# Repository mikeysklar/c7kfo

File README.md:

# c7kfo
c7k flat out

Two handed super flat chording keyboard.

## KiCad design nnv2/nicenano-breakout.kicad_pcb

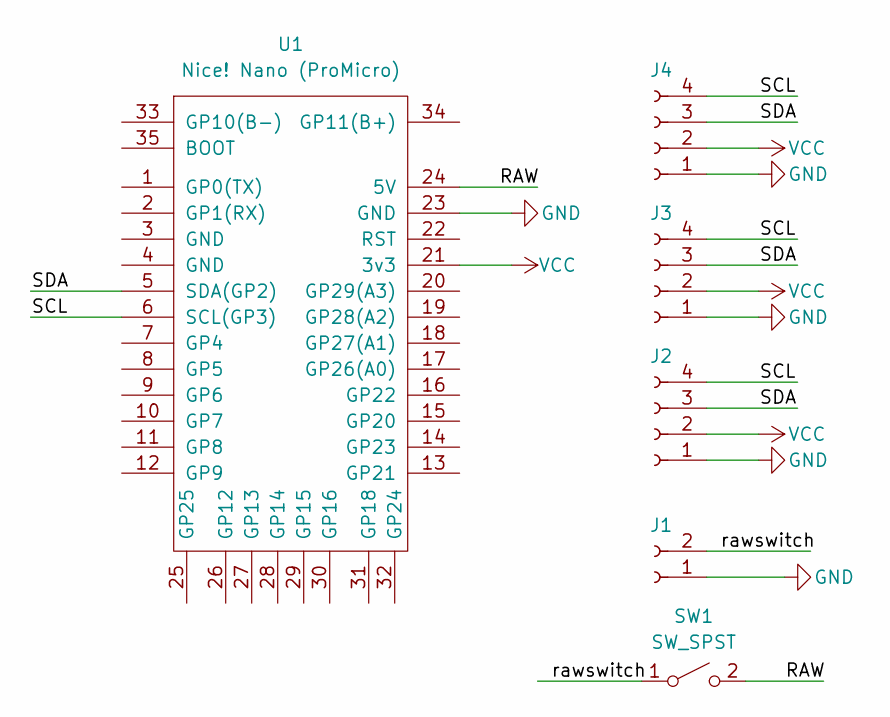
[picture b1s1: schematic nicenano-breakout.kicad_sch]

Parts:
J1: Conn_01x02_Socket; JST_PH_S2B-PH-SM4-TB_1x02-1MP_P2.00mm_Horizontal
J2, J3, J4: Conn_01x04_Socket; JST_SH4
SW1: SW_SPST; SW_SPDT_CK_JS102011SAQN
U1: Nice! Nano (ProMicro); SuperMini NRF52840

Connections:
/RAW: SW1.2 (B), U1.24 (5V)
/SCL: J2.4, J3.4, J4.4, U1.6 (SCL(GP3))
/SDA: J2.3, J3.3, J4.3, U1.5 (SDA(GP2))
/rawswitch: J1.2, SW1.1 (A)
GND: J1.1, J2.1, J3.1, J4.1, U1.23 (GND)
VCC: J2.2, J3.2, J4.2, U1.21 (3v3)

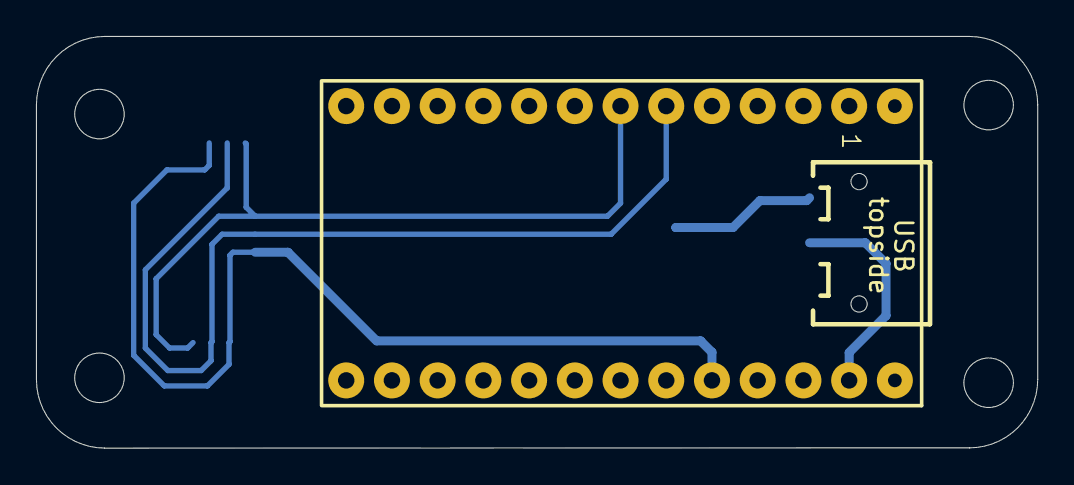
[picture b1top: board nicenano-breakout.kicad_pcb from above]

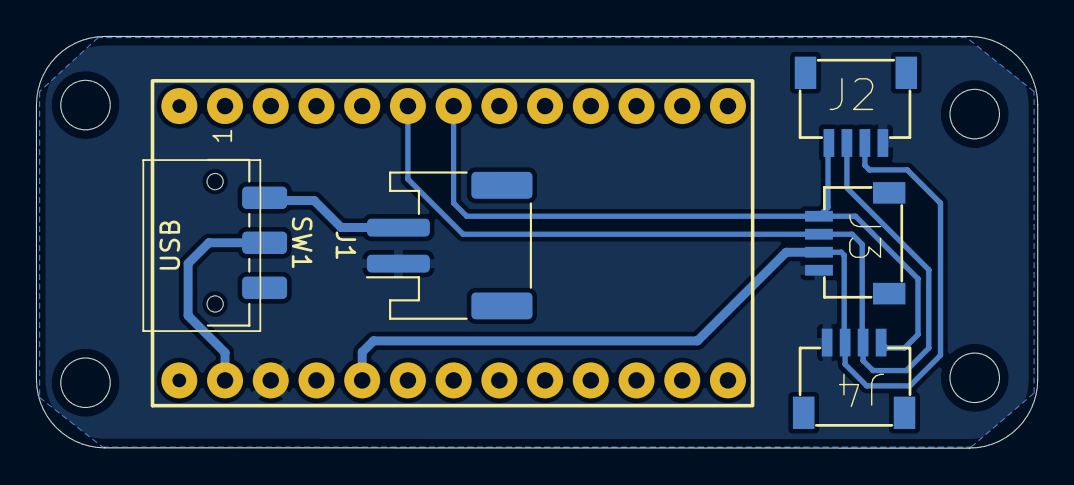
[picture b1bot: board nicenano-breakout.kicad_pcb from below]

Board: 2 copper layers, 55.6 x 22.9 mm, 6 parts (5 on the bottom side), 6 nets.

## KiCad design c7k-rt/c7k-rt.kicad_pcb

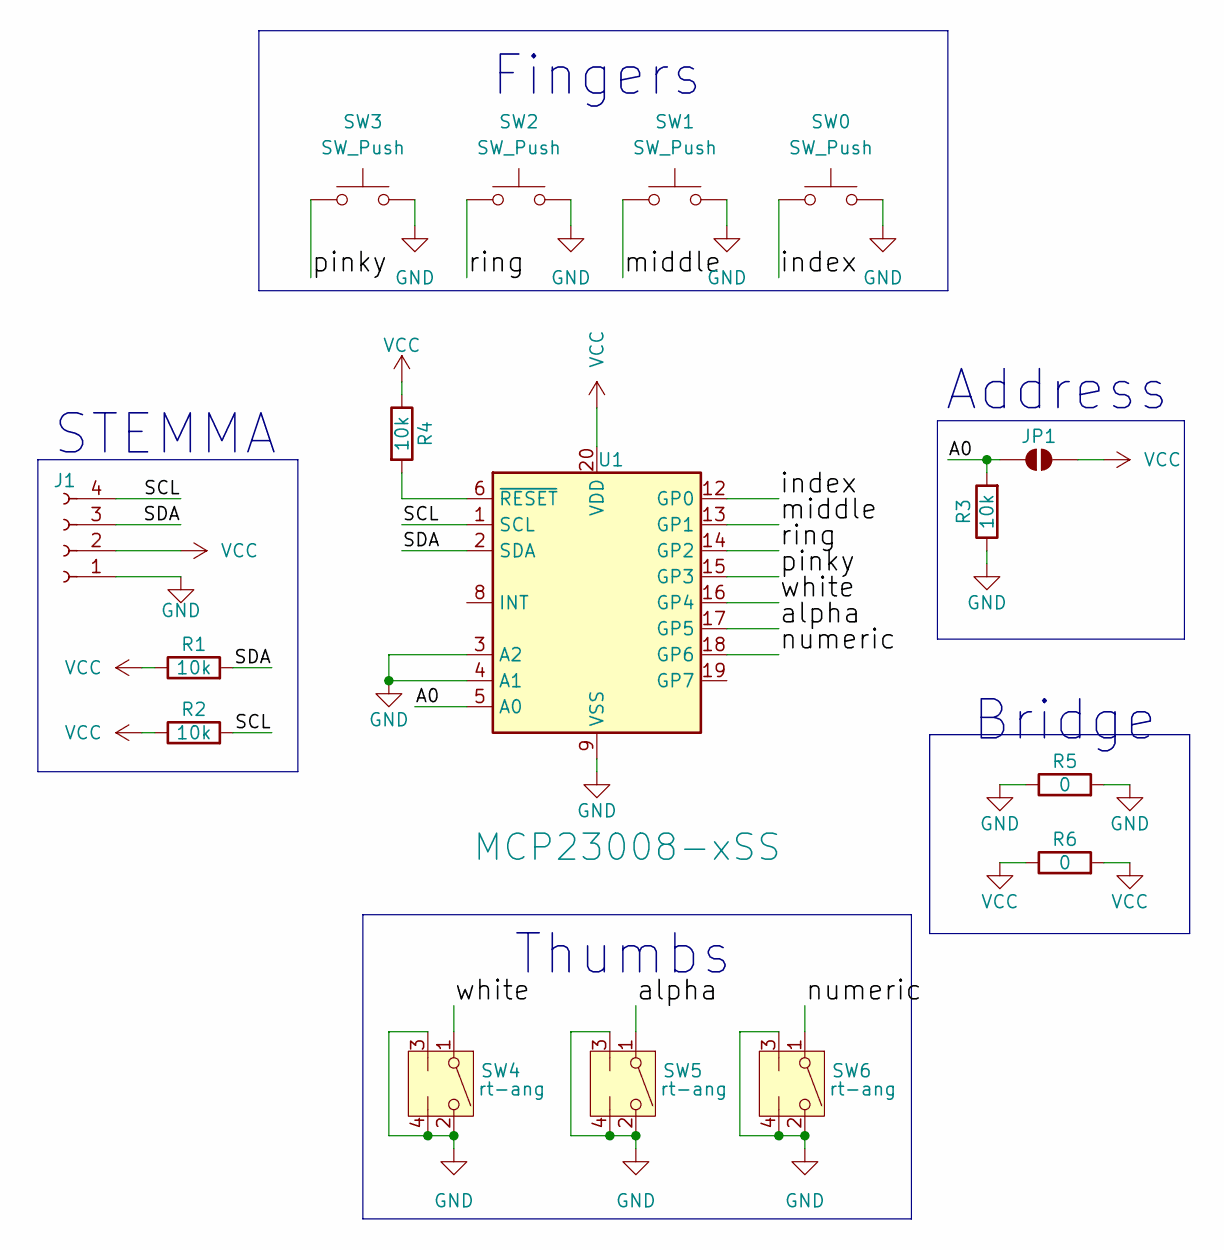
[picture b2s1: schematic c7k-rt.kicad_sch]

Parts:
J1: Conn_01x04_Socket; JST_SH_SM04B-SRSS-TB_1x04-1MP_P1.00mm_Horizontal
JP1: SolderJumper_2_Open; SolderJumper-2_P1.3mm_Open_TrianglePad1.0x1.5mm
R1, R2, R3, R4: 10k; R_0805_2012Metric_Pad1.20x1.40mm_HandSolder
R5, R6: 0; R_0805_2012Metric_Pad1.20x1.40mm_HandSolder
SW0, SW1, SW2, SW3: SW_Push; Kailh_socket_PG1350
SW4, SW5, SW6: rt-ang; SW_Tactile_SPST_Angled_PTS645Vx83-2LFS
U1: MCP23008-xSS; SSOP-20_5.3x7.2mm_P0.65mm

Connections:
/A0: JP1.1 (A), R3.2, U1.5 (A0)
/SCL: J1.4, R2.2, U1.1 (SCL)
/SDA: J1.3, R1.2, U1.2 (SDA)
/alpha: SW5.1, U1.17 (GP5)
/index: SW0.1, U1.12 (GP0)
/middle: SW1.1, U1.13 (GP1)
/numeric: SW6.1, U1.18 (GP6)
/pinky: SW3.1, U1.15 (GP3)
/ring: SW2.1, U1.14 (GP2)
/white: SW4.1, U1.16 (GP4)
GND: J1.1, R3.1, R5.1, R5.2, SW0.2, SW1.2, SW2.2, SW3.2, SW4.2, SW4.3 (L), SW4.4 (L), SW5.2, SW5.3 (L), SW5.4 (L), SW6.2, SW6.3 (L), SW6.4 (L), U1.3 (A2), U1.4 (A1), U1.9 (VSS)
unnamed: R4.2, U1.6 (~RESET)
VCC: J1.2, JP1.2 (B), R1.1, R2.1, R4.1, R6.1, R6.2, U1.20 (VDD)

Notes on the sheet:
Bridge
Fingers
Thumbs
Address
STEMMA

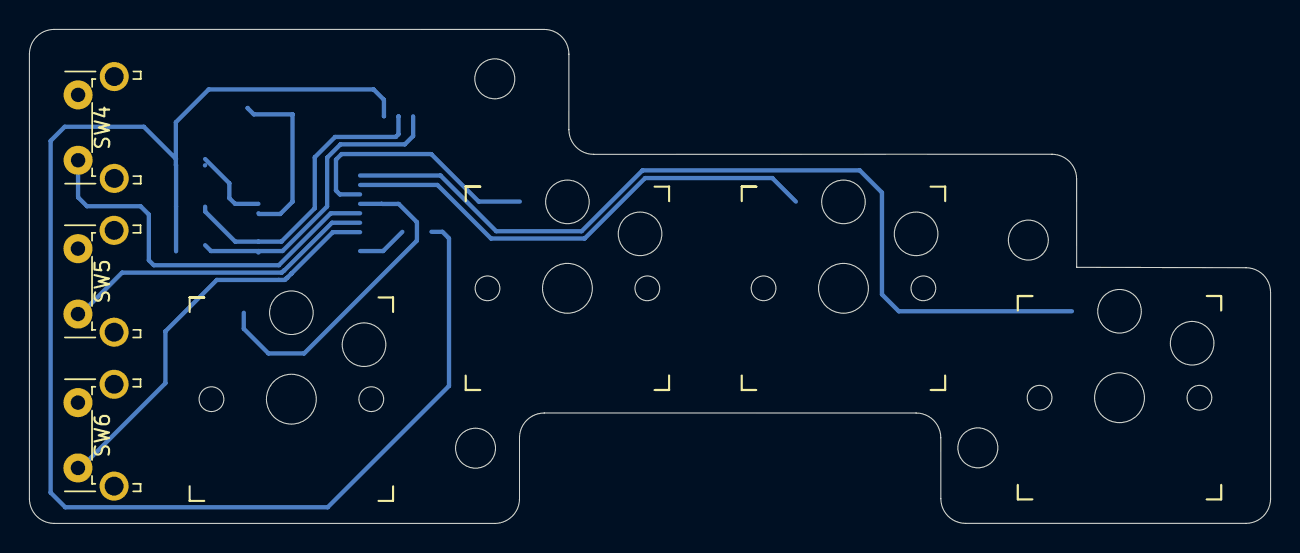
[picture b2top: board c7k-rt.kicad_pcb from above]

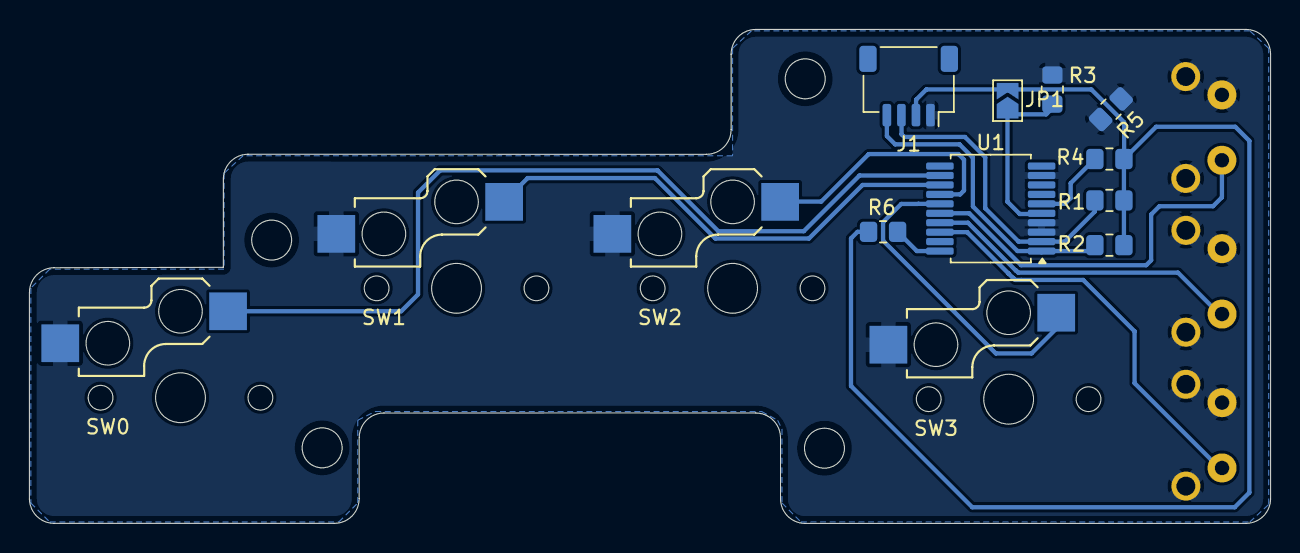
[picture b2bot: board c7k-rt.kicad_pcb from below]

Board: 2 copper layers, 85.4 x 34.0 mm, 16 parts (9 on the bottom side), 13 nets.

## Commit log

2025-05-01 init
2025-05-02 added right keyboard support
    right side keyboard functional
2025-05-02 added ctrl/shift/gui and mouse
2025-05-06 updated layer code
2025-05-06 images
